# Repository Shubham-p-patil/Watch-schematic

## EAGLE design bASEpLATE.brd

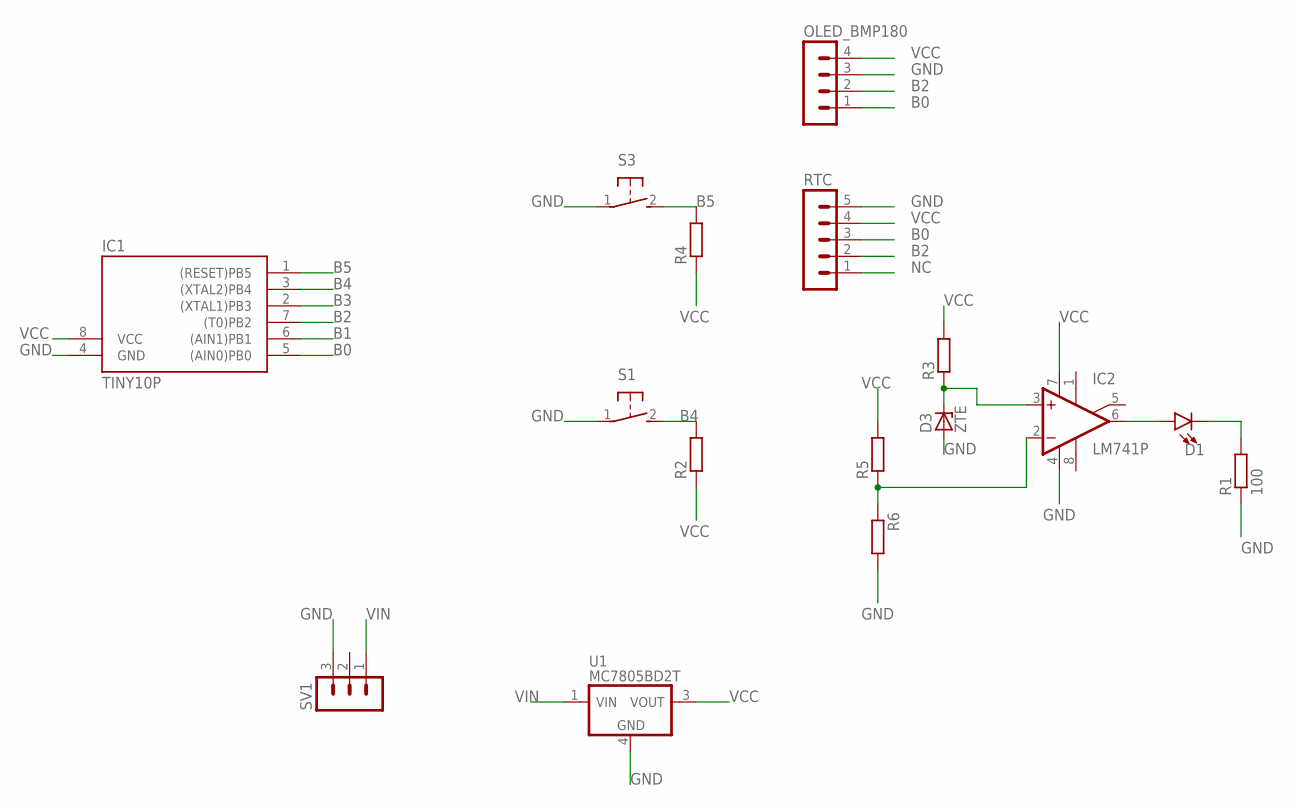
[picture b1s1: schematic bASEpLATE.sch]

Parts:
D1: LED-3MM-NO_SILK; LED_3MM-NS
D3: ZTE; DO35Z10
IC1: TINY10P; DIL08
IC2: LM741P; DIL08
OLED_BMP180: MA04-1
R1: 100; 0204/7
R2, R3, R4, R5, R6: R-EU_0204/7; 0204/7
RTC: MA05-1
S1, S3: 31-XX; B3F-31XX
SV1: MA03-1
U1: MC7805BD2T; D2PAK-3

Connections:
B0: IC1.5 ((AIN0)PB0), OLED_BMP180.1, RTC.3
B1: IC1.6 ((AIN1)PB1)
B2: IC1.7 ((T0)PB2), OLED_BMP180.2, RTC.2
B3: IC1.2 ((XTAL1)PB3)
B4: IC1.3 ((XTAL2)PB4), R2.2, S1.2 (S)
B5: IC1.1 ((RESET)PB5), R4.2, S3.2 (S)
GND: D3.A, IC1.4 (GND), IC2.4 (V-), OLED_BMP180.3, R1.1, R6.2, RTC.5, S1.1, S3.1, SV1.3, U1.4 (GND)
unnamed: D1.A, IC2.6 (OUT)
unnamed: IC2.2 (-IN), R5.1, R6.1
unnamed: D3.C, IC2.3 (+IN), R3.1
unnamed: D1.K (C), R1.2
NC: RTC.1
VCC: IC1.8 (VCC), IC2.7 (V+), OLED_BMP180.4, R2.1, R3.2, R4.1, R5.2, RTC.4, U1.3 (VOUT)
VIN: SV1.1, U1.1 (VIN)

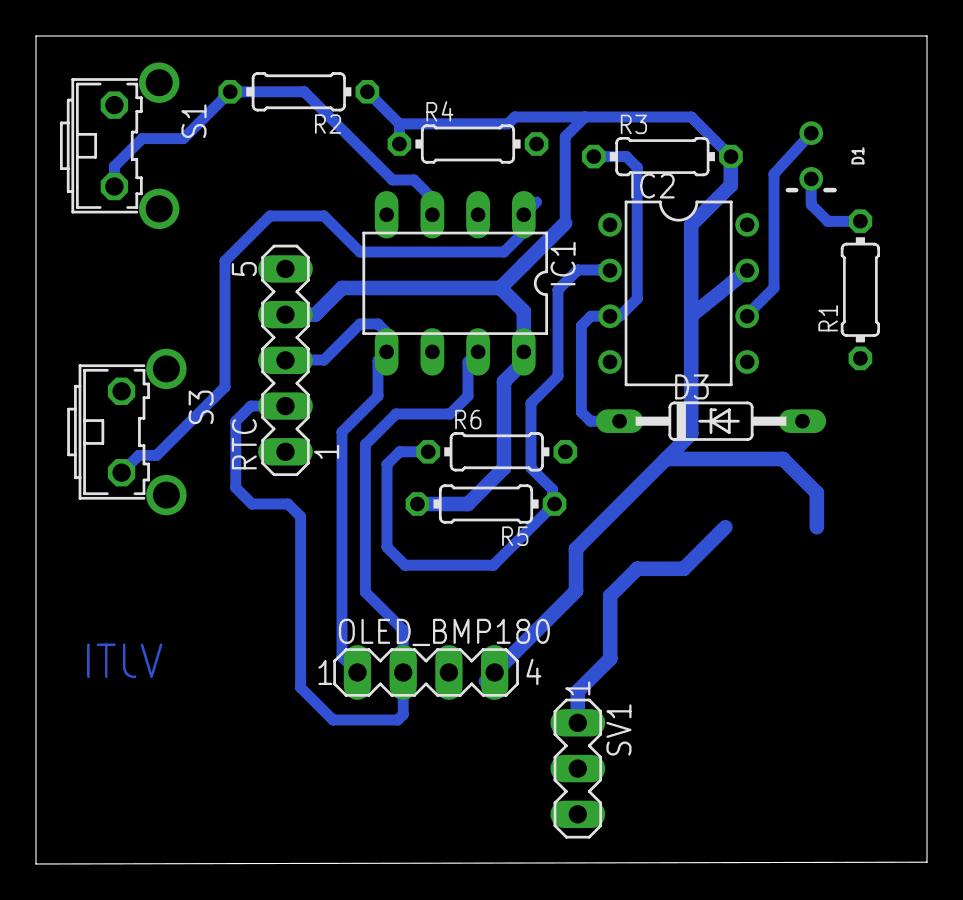
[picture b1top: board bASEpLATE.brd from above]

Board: 2 copper layers, 49.5 x 46.0 mm, 16 parts (1 on the bottom side), 11 nets.

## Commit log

2017-11-08 Switch Pulled High And 7805 mirrored

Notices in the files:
parts and their libraries:
SparkFun-LED: Licensing: Creative Commons ShareAlike 4.0 International - https://creativecommons.org/licenses/by-sa/4.0
